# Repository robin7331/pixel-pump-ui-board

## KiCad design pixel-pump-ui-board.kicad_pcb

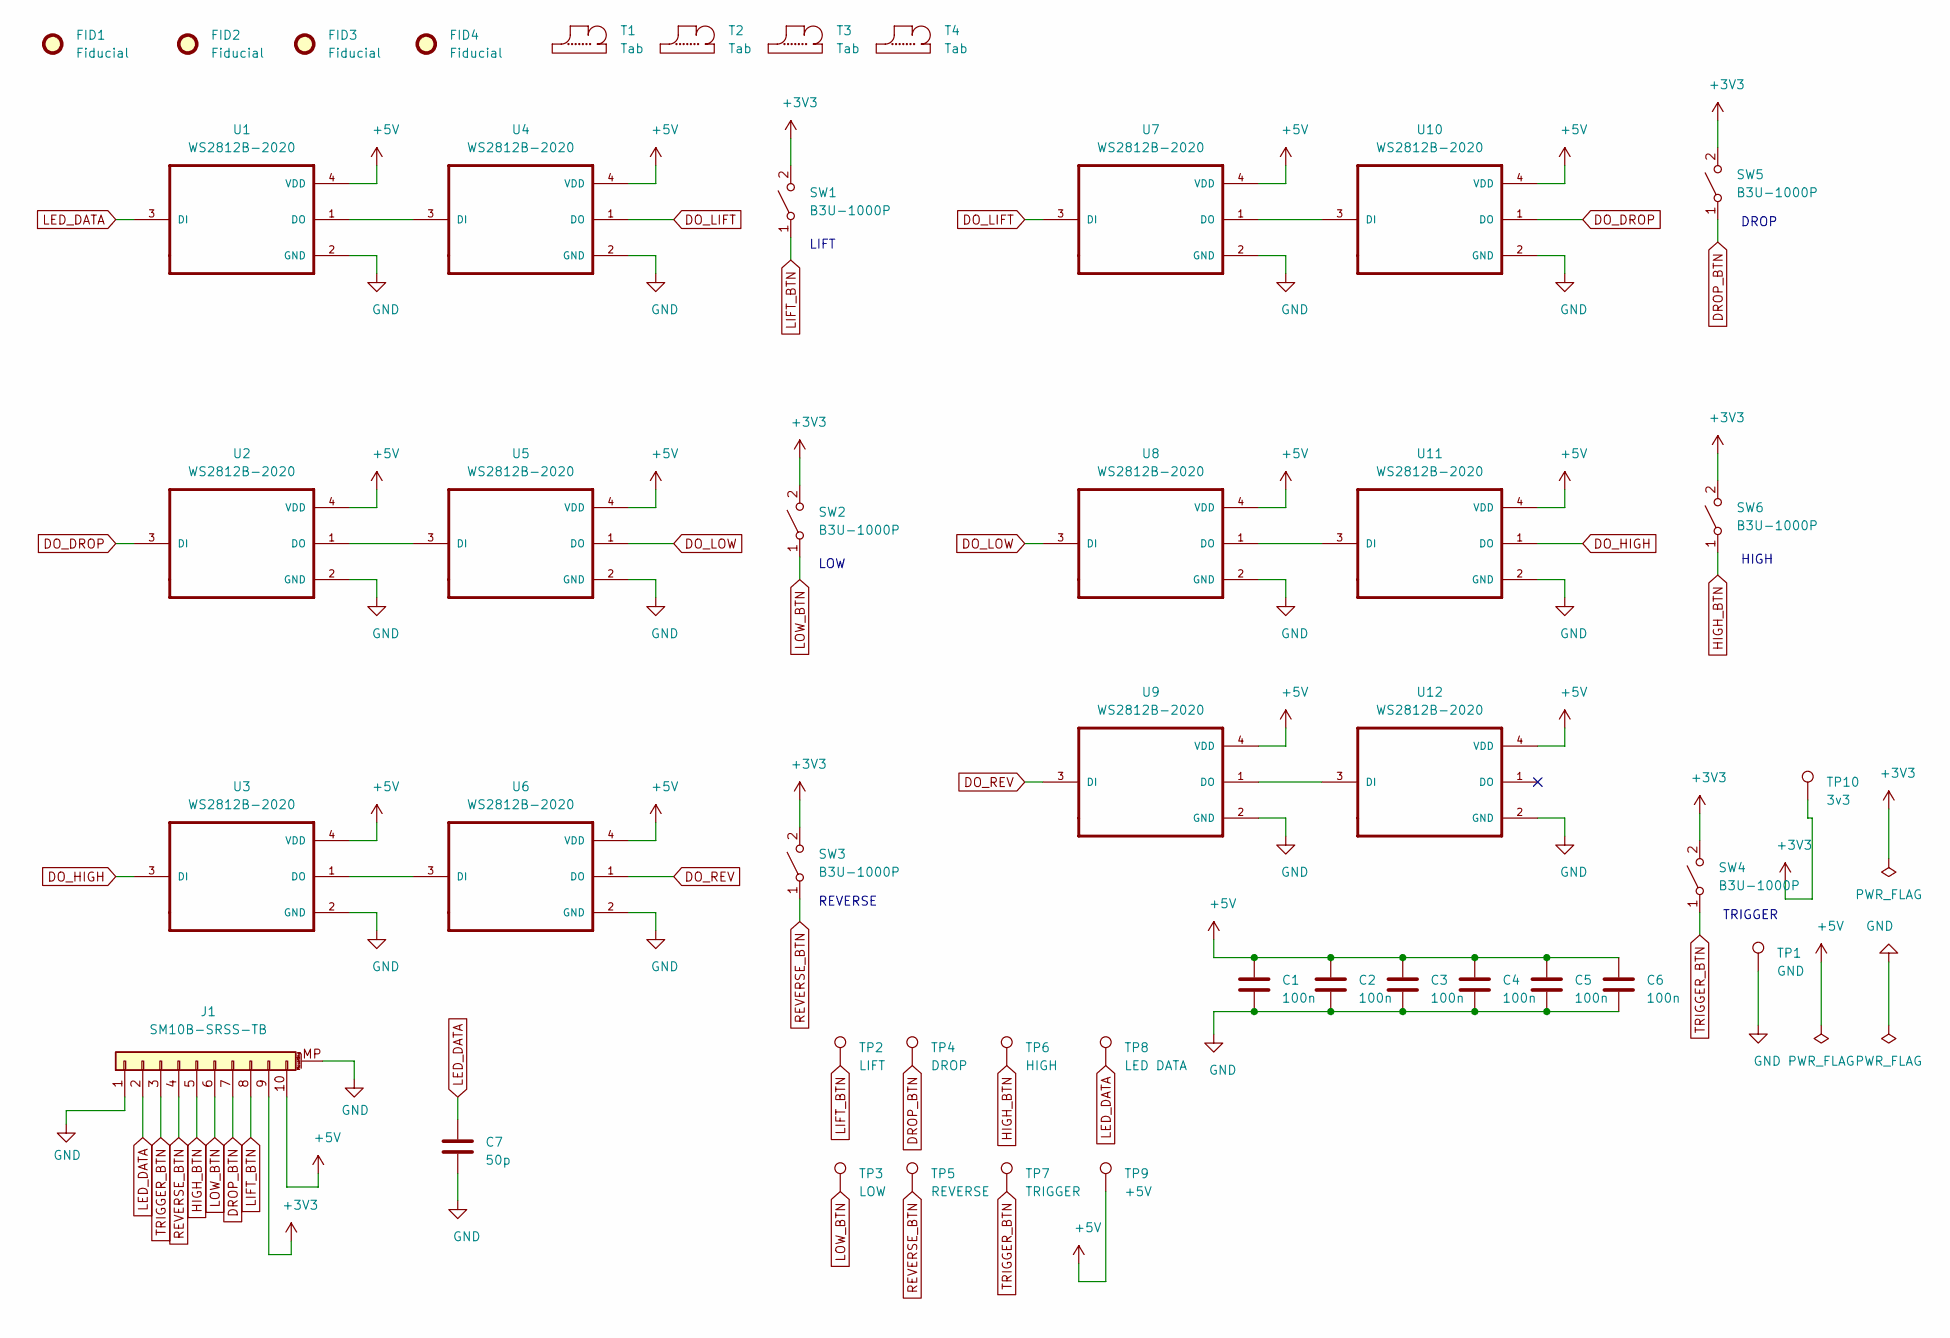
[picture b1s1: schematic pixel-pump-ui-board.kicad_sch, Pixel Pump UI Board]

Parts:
C1, C2, C3, C4, C5, C6: 100n; C_0603_1608Metric; MPN 100n 0603
C7: 50p; C_0603_1608Metric; MPN 50p 0603
FID1, FID2, FID3, FID4: Fiducial; Fiducial_0.75mm_Mask1.5mm
J1: SM10B-SRSS-TB; MPN SM10B-SRSS-TB(LF)(SN)
SW1, SW2, SW3, SW4, SW5, SW6: B3U-1000P; SW_SPST_B3U-1000P; MPN B3U-1000P
T1, T2, T3, T4: Tab
TP1: GND; TestPoint_Pad_D1.5mm
TP2: LIFT; TestPoint_Pad_D1.5mm
TP3: LOW; TestPoint_Pad_D1.5mm
TP4: DROP; TestPoint_Pad_D1.5mm
TP5: REVERSE; TestPoint_Pad_D1.5mm
TP6: HIGH; TestPoint_Pad_D1.5mm
TP7: TRIGGER; TestPoint_Pad_D1.5mm
TP8: LED DATA; TestPoint_Pad_D1.5mm
TP9: +5V; TestPoint_Pad_D1.5mm
TP10: 3v3; TestPoint_Pad_D1.5mm
U1, U2, U3, U4, U5, U6, U7, U8, U9, U10, U11, U12: WS2812B-2020; LED_WS2812-2020; MPN WS2812B-2020

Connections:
+3V3: J1.9, SW1.2 (B), SW2.2 (B), SW3.2 (B), SW4.2 (B), SW5.2 (B), SW6.2 (B), TP10.1
+5V: C1.1, C2.1, C3.1, C4.1, C5.1, C6.1, J1.10, TP9.1, U1.4 (VDD), U2.4 (VDD), U3.4 (VDD), U4.4 (VDD), U5.4 (VDD), U6.4 (VDD), U7.4 (VDD), U8.4 (VDD), U9.4 (VDD), U10.4 (VDD), U11.4 (VDD), U12.4 (VDD)
DO_DROP: U2.3 (DI), U10.1 (DO)
DO_HIGH: U3.3 (DI), U11.1 (DO)
DO_LIFT: U4.1 (DO), U7.3 (DI)
DO_LOW: U5.1 (DO), U8.3 (DI)
DO_REV: U6.1 (DO), U9.3 (DI)
DROP_BTN: J1.7, SW5.1 (A), TP4.1
GND: C1.2, C2.2, C3.2, C4.2, C5.2, C6.2, C7.2, J1.1, J1.MP (MountPin), TP1.1, U1.2 (GND), U2.2 (GND), U3.2 (GND), U4.2 (GND), U5.2 (GND), U6.2 (GND), U7.2 (GND), U8.2 (GND), U9.2 (GND), U10.2 (GND), U11.2 (GND), U12.2 (GND)
HIGH_BTN: J1.5, SW6.1 (A), TP6.1
LED_DATA: C7.1, J1.2, TP8.1, U1.3 (DI)
LIFT_BTN: J1.8, SW1.1 (A), TP2.1
LOW_BTN: J1.6, SW2.1 (A), TP3.1
unnamed: U1.1 (DO), U4.3 (DI)
unnamed: U2.1 (DO), U5.3 (DI)
unnamed: U3.1 (DO), U6.3 (DI)
unnamed: U7.1 (DO), U10.3 (DI)
unnamed: U8.1 (DO), U11.3 (DI)
unnamed: U9.1 (DO), U12.3 (DI)
REVERSE_BTN: J1.4, SW3.1 (A), TP5.1
TRIGGER_BTN: J1.3, SW4.1 (A), TP7.1

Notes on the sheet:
REVERSE
DROP
HIGH
LIFT
TRIGGER
LOW

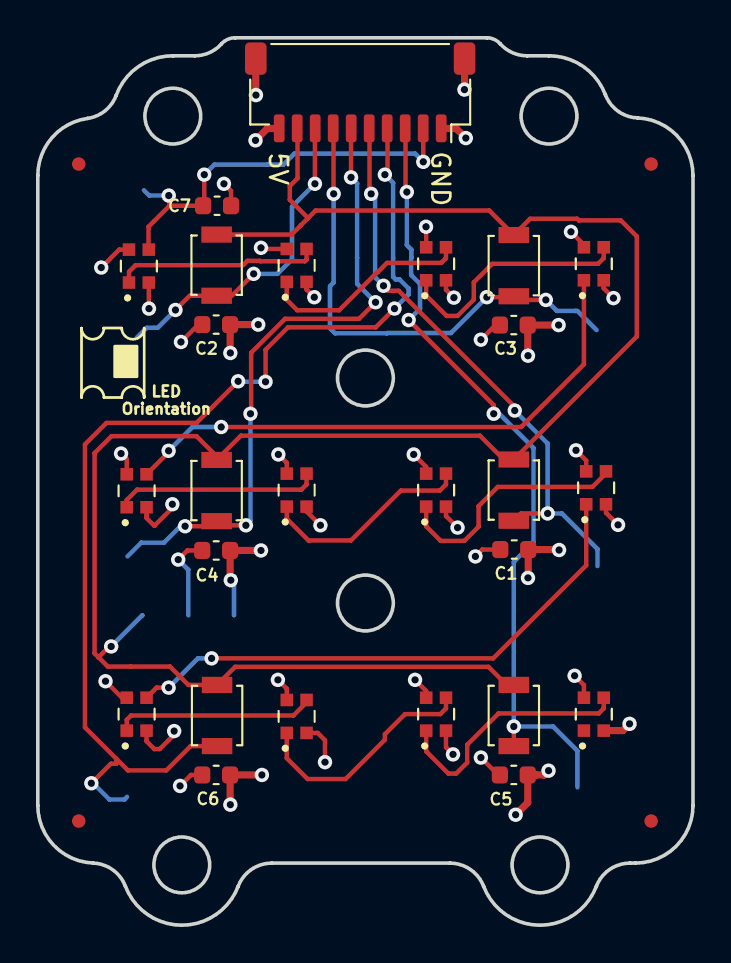
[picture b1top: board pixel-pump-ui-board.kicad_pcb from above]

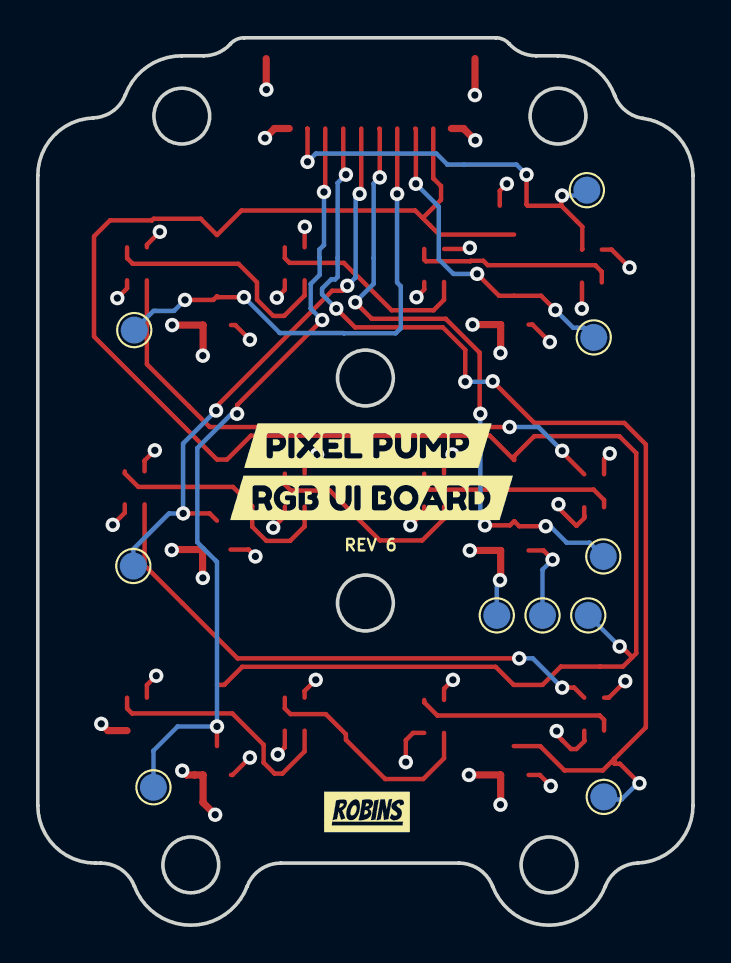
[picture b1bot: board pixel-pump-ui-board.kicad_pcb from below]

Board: 4 copper layers, 36.4 x 49.3 mm, 46 parts (12 on the bottom side), 21 nets.

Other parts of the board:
kibuzzard-6108471A: G***; kibuzzard-6108471A
kibuzzard-61084704: G***; kibuzzard-61084704

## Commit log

2021-03-05 Finish v1.0 and create gerbers
2021-03-05 Update design and generate gerbers
2021-03-08 cleanup
2021-03-09 Added 3D model to molex FFC cable
2021-03-09 STEP export
2021-03-11 Flipped FFC connector and generated gerbers
2021-03-24 updated iBOM
2021-05-20 Updated and ordered ref 2
2021-07-13 BOM Export
2021-07-13 Generate iBOM
2021-08-02 Refactorings
2021-08-02 Minor things
2021-08-03 add gitignore
2021-08-03 Remove old path from gitignore
2021-08-03 Ignore backups
2021-08-06 Cleanup and generate iBOM
2021-08-06 Generate rev2 gerbers
2022-01-11 Update project to Kicad 6
2022-01-11 Rename project files to pixel-pump
2022-01-11 Sorted components and updated schematics title
2022-01-16 Updated ref label on board
2022-01-16 Update gitignore
2022-01-16 Add penelize scripts
2022-01-16 Update bom
2022-02-23 Update iBOM
2022-04-29 Reduce stiffness of mousebites
2022-08-04 Add side load connector to PCB & MPN to all parts
2022-08-04 Add robins logo
2022-08-04 Update appearance
2022-12-22 iBOM
2023-01-31 Add fiducials and open mounting holes from 2.9 to 3.1 mm
2023-01-31 Fill areas
2023-02-13 Remove gerber output from gitignore
2023-02-13 Add KiKit Tabs
2023-02-13 Panelize and add gerbers for a 2 x 3 panel
2023-02-24 Panelize
2023-03-08 Fix pnp csv file
